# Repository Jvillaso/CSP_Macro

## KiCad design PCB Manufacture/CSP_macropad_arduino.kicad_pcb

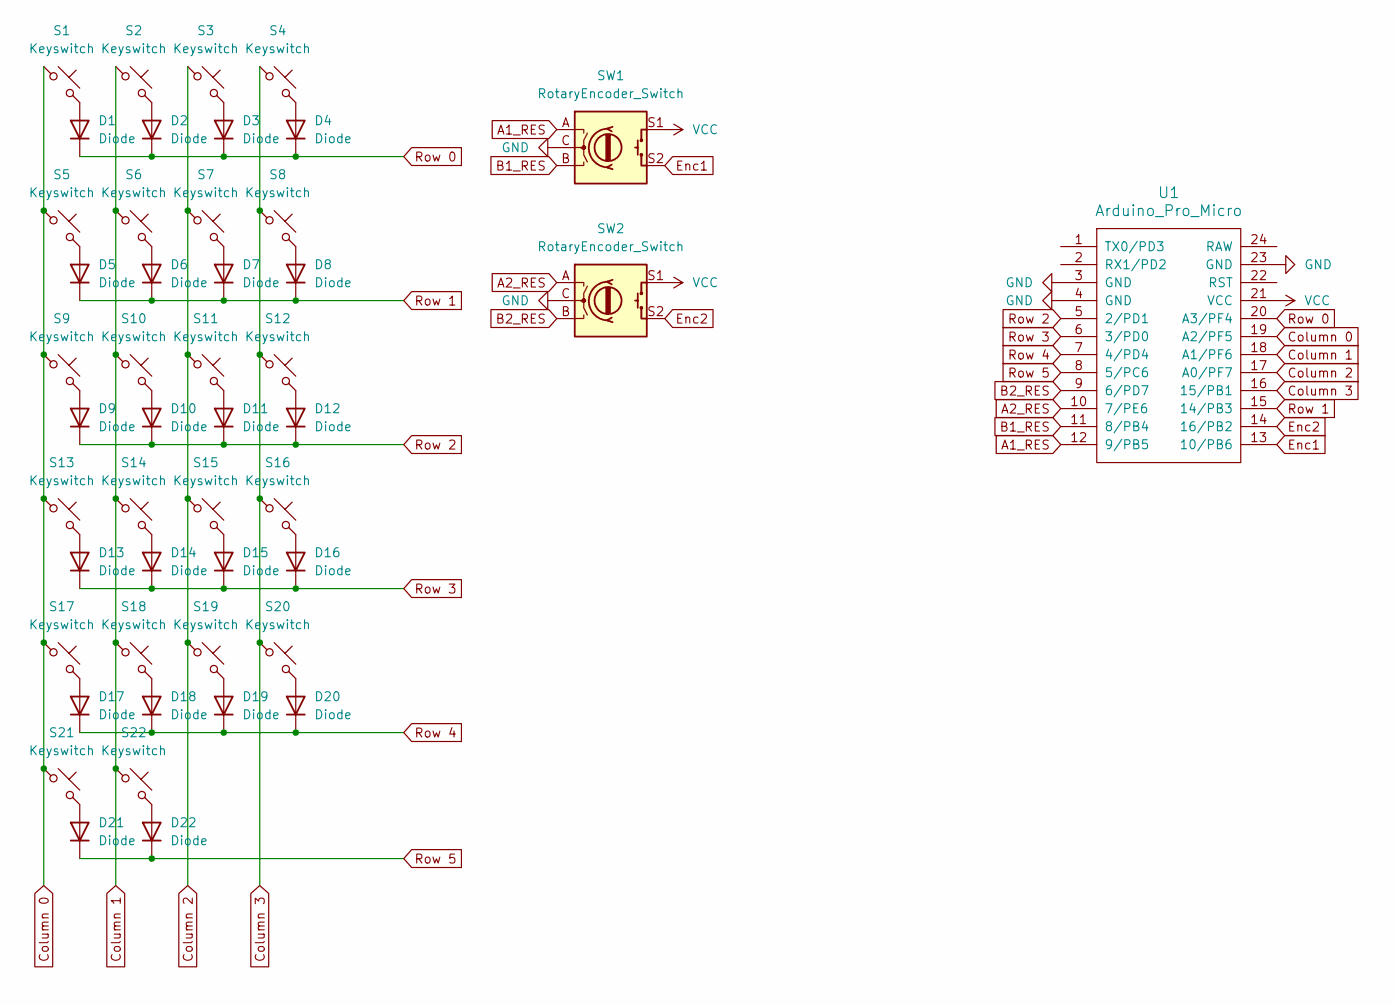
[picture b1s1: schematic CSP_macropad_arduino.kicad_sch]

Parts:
D1, D2, D3, D4, D5, D6, D7, D8, D9, D10, D11, D12, D13, D14, D15, D16, D17, D18, D19, D20, D21, D22: Diode; Diode_SOD-123
S1, S2, S3, S4, S5, S6, S7, S8, S9, S10, S11, S12, S13, S14, S15, S16, S17, S18, S19, S21: Keyswitch; Hotswap_MX_1.00u
S20: Keyswitch; Hotswap_MX_2.00u_90deg
S22: Keyswitch; Hotswap_MX_2.00u
SW1, SW2: RotaryEncoder_Switch; RotaryEncoder_EC11
U1: Arduino_Pro_Micro

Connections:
A1_RES: SW1.A, U1.12 (9/PB5)
A2_RES: SW2.A, U1.10 (7/PE6)
B1_RES: SW1.B, U1.11 (8/PB4)
B2_RES: SW2.B, U1.9 (6/PD7)
Column 0: S1.1, S5.1, S9.1, S13.1, S17.1, S21.1, U1.19 (A2/PF5)
Column 1: S2.1, S6.1, S10.1, S14.1, S18.1, S22.1, U1.18 (A1/PF6)
Column 2: S3.1, S7.1, S11.1, S15.1, S19.1, U1.17 (A0/PF7)
Column 3: S4.1, S8.1, S12.1, S16.1, S20.1, U1.16 (15/PB1)
Enc1: SW1.S2, U1.13 (10/PB6)
Enc2: SW2.S2, U1.14 (16/PB2)
GND: SW1.C, SW2.C, U1.3 (GND), U1.4 (GND), U1.23 (GND)
unnamed: D1.2 (A), S1.2
unnamed: D2.2 (A), S2.2
unnamed: D3.2 (A), S3.2
unnamed: D4.2 (A), S4.2
unnamed: D5.2 (A), S5.2
unnamed: D6.2 (A), S6.2
unnamed: D7.2 (A), S7.2
unnamed: D8.2 (A), S8.2
unnamed: D9.2 (A), S9.2
unnamed: D10.2 (A), S10.2
unnamed: D11.2 (A), S11.2
unnamed: D12.2 (A), S12.2
unnamed: D13.2 (A), S13.2
unnamed: D14.2 (A), S14.2
unnamed: D15.2 (A), S15.2
unnamed: D16.2 (A), S16.2
unnamed: D17.2 (A), S17.2
unnamed: D18.2 (A), S18.2
unnamed: D19.2 (A), S19.2
unnamed: D20.2 (A), S20.2
unnamed: D21.2 (A), S21.2
unnamed: D22.2 (A), S22.2
Row 0: D1.1 (K), D2.1 (K), D3.1 (K), D4.1 (K), U1.20 (A3/PF4)
Row 1: D5.1 (K), D6.1 (K), D7.1 (K), D8.1 (K), U1.15 (14/PB3)
Row 2: D9.1 (K), D10.1 (K), D11.1 (K), D12.1 (K), U1.5 (2/PD1)
Row 3: D13.1 (K), D14.1 (K), D15.1 (K), D16.1 (K), U1.6 (3/PD0)
Row 4: D17.1 (K), D18.1 (K), D19.1 (K), D20.1 (K), U1.7 (4/PD4)
Row 5: D21.1 (K), D22.1 (K), U1.8 (5/PC6)
VCC: SW1.S1, SW2.S1, U1.21 (VCC)

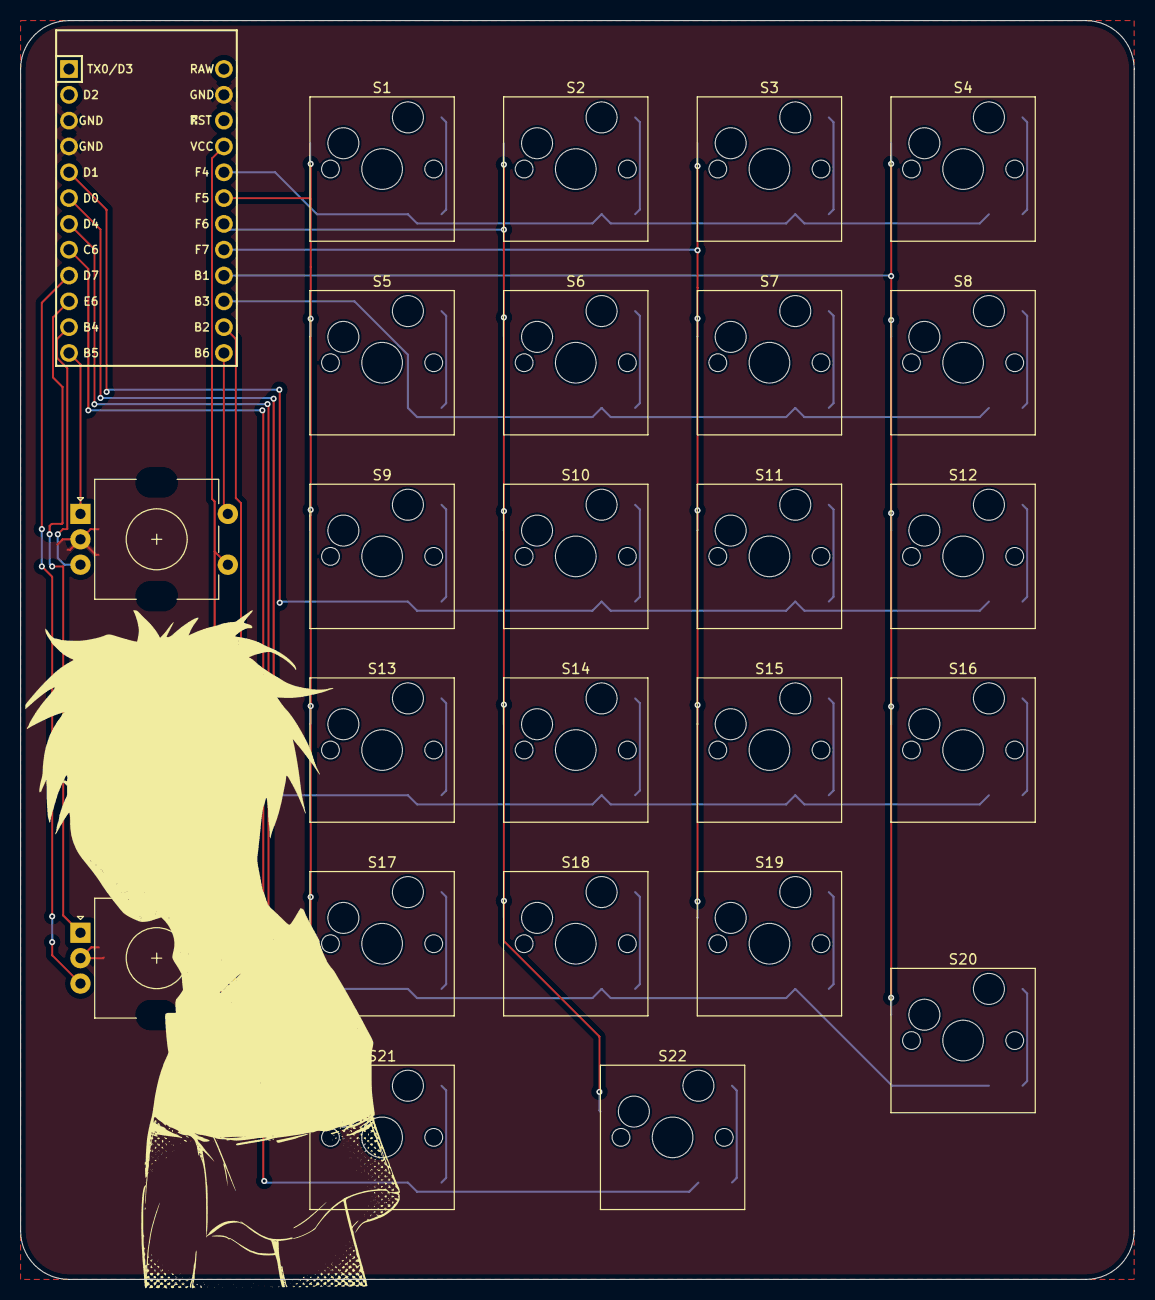
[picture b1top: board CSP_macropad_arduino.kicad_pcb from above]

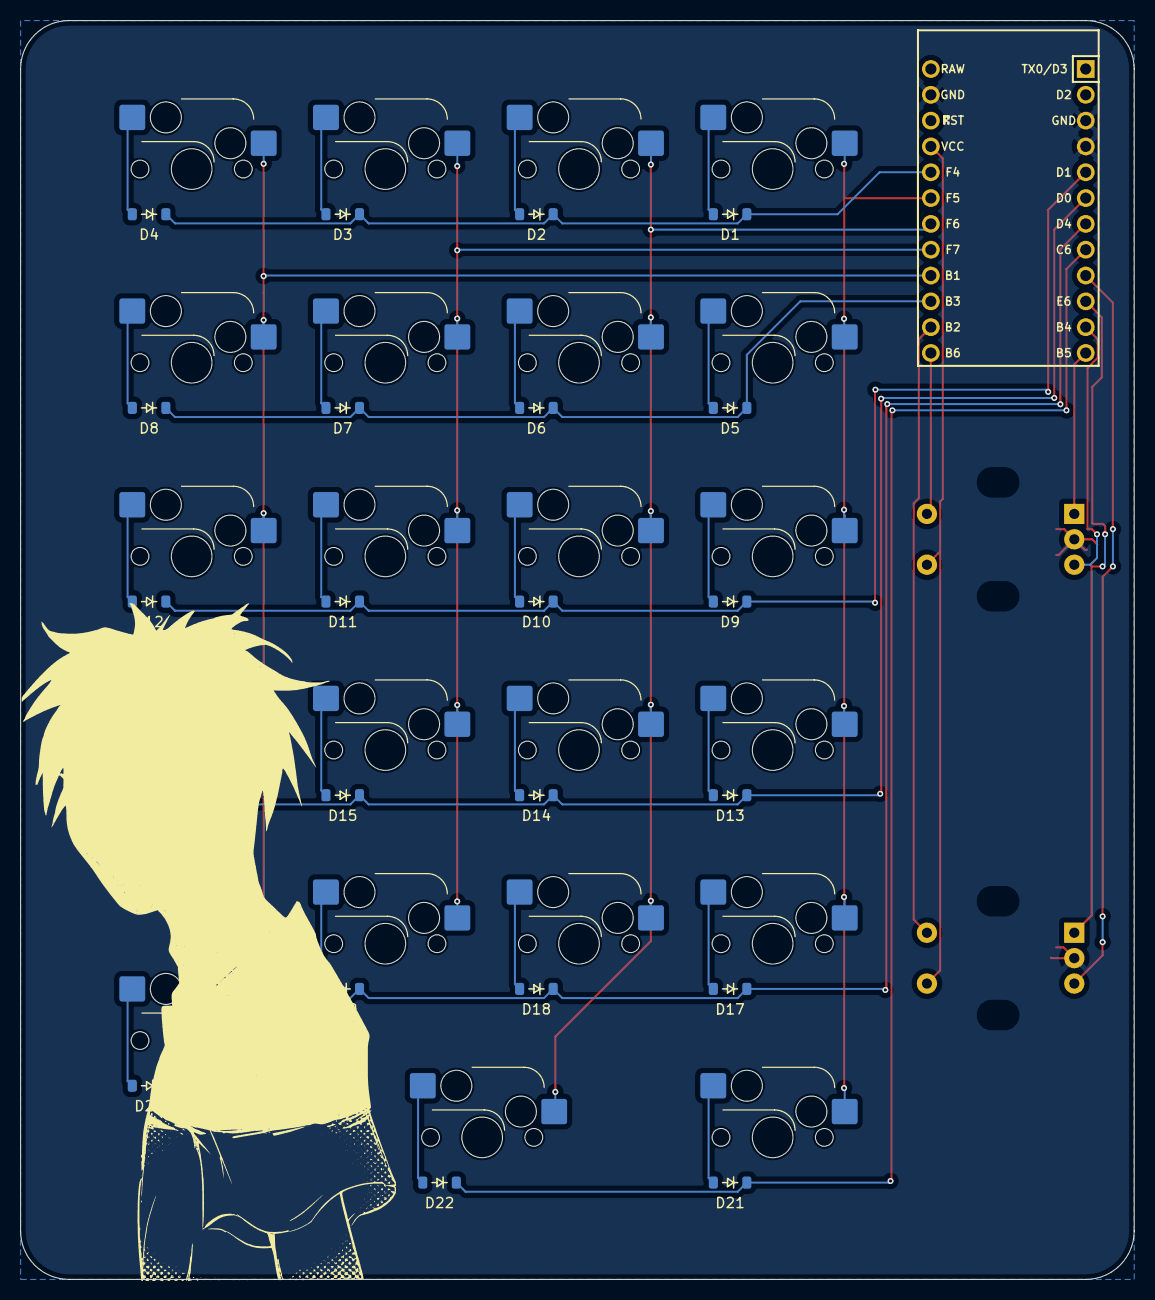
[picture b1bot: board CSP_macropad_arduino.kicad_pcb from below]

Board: 2 copper layers, 109.6 x 123.9 mm, 47 parts (22 on the bottom side), 40 nets.

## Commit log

2024-06-11 Upload, V1 CSP_Macro
2024-06-13 Cleaned
